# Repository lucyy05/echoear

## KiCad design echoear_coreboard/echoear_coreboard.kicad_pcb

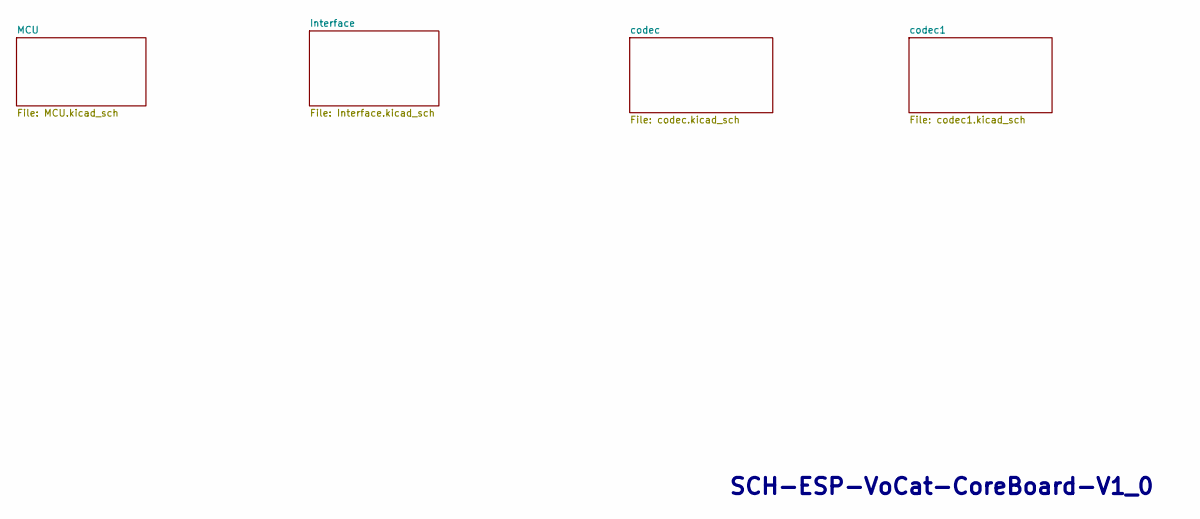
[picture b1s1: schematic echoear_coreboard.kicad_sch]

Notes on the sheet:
SCH-ESP-VoCat-CoreBoard-V1_0

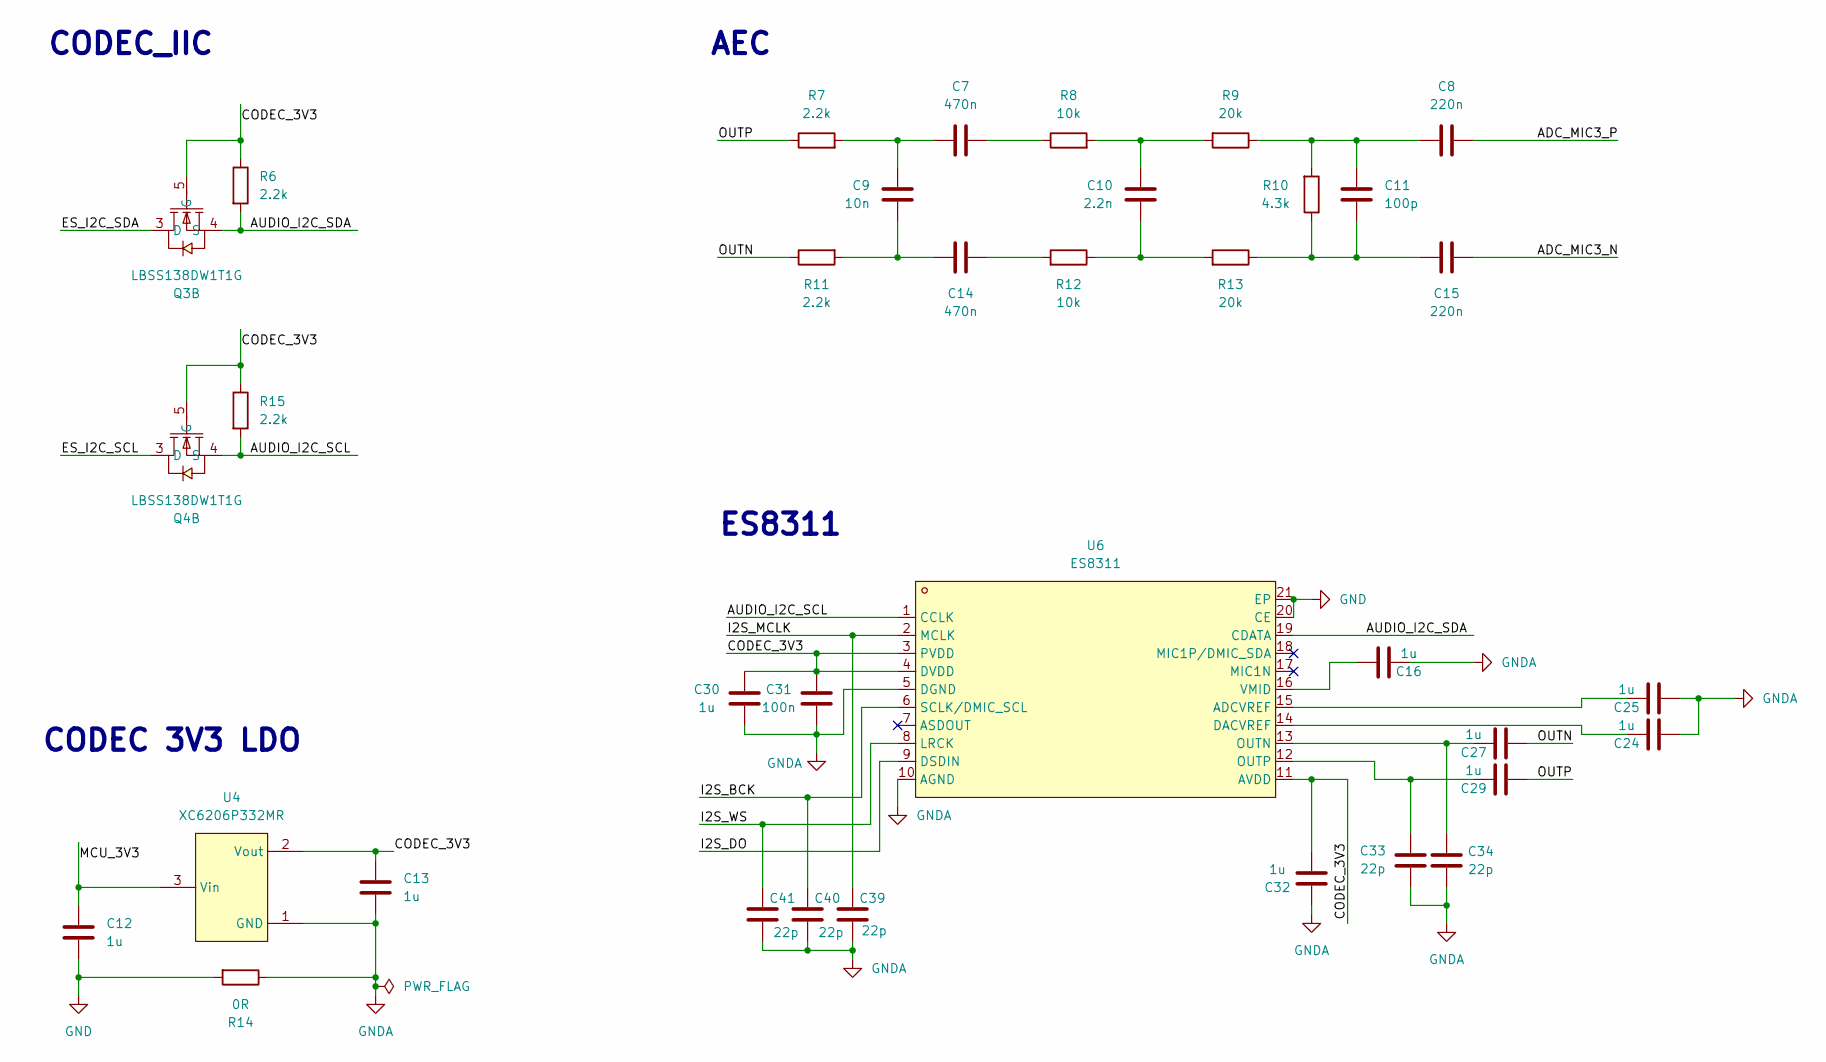
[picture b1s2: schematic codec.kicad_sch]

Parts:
C7, C14: 470n; C_0402_1005Metric; LCSC C437527
C8, C15: 220n; C_0402_1005Metric; LCSC C16772
C9: 10n; C_0402_1005Metric; LCSC C15195
C10: 2.2n; C_0402_1005Metric; LCSC C2987940
C11: 100p; C_0402_1005Metric; LCSC C1546
C12, C13, C16, C24, C25, C27, C29, C30, C32: 1u; C_0402_1005Metric; LCSC C52923
C31: 100n; C_0402_1005Metric; LCSC C1525
C33, C34, C39, C40, C41: 22p; C_0402_1005Metric; LCSC C1555
Q3, Q4: LBSS138DW1T1G; SC-88-6_L2.0-W1.3-P0.65-LS2.1-BL; MPN LBSS138DW1T1G; LCSC Part C525406
R6, R7, R11, R15: 2.2k; R_0402_1005Metric; LCSC C25879
R8, R12: 10k; R_0402_1005Metric; LCSC C25744
R9: 20k; R_0402_1005Metric; LCSC C25765
R10: 4.3k; C_0402_1005Metric; LCSC C477725
R13: 20k; C_0402_1005Metric; LCSC C25765
R14: 0R; R_0402_1005Metric; LCSC C17168
U4: XC6206P332MR; SOT-23-3_L2.9-W1.6-P1.90-LS2.8-BR; MPN XC6206P332MR-G; LCSC Part C5446
U6: ES8311; WQFN-20_L3.0-W3.0-P0.40-BL-EP1.7; MPN ES8311; LCSC Part C962342

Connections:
/codec/ADC_MIC3_N: C15.1
/codec/ADC_MIC3_P: C8.1
/codec/AUDIO_I2C_SCL: Q4.4 (S), R15.2, U6.1 (CCLK)
/codec/AUDIO_I2C_SDA: Q3.4 (S), R6.2, U6.19 (CDATA)
/codec/CODEC_3V3: C13.1, C30.2, C31.2, C32.2, Q3.5 (G), Q4.5 (G), R6.1, R15.1, U4.2 (Vout), U6.3 (PVDD), U6.4 (DVDD), U6.11 (AVDD)
/codec/ES_I2C_SCL: Q4.3 (D)
/codec/ES_I2C_SDA: Q3.3 (D)
/codec/I2S_BCK: C40.2, U6.6 (SCLK/DMIC_SCL)
/codec/I2S_DO: U6.9 (DSDIN)
/codec/I2S_MCLK: C39.2, U6.2 (MCLK)
/codec/I2S_WS: C41.2, U6.8 (LRCK)
/codec/MCU_3V3: C12.1, U4.3 (Vin)
/codec/OUTN: C27.2, R11.1
/codec/OUTP: C29.2, R7.1
GND: C12.2, R14.2, U6.20 (CE), U6.21 (EP); also elsewhere on the board
GNDA: C13.2, C16.2, C24.2, C25.2, C30.1, C31.1, C32.1, C33.1, C34.2, C39.1, C40.1, C41.1, R14.1, U4.1 (GND), U6.5 (DGND), U6.10 (AGND); also elsewhere on the board
unnamed: C7.1, C9.1, R7.2
unnamed: C7.2, R8.1
unnamed: C10.1, R8.2, R9.2
unnamed: C10.2, R12.1, R13.2
unnamed: C8.2, C11.1, R9.1, R10.2
unnamed: C11.2, C15.2, R10.1, R13.1
unnamed: C14.1, R12.2
unnamed: C9.2, C14.2, R11.2
unnamed: C25.1, U6.15 (ADCVREF)
unnamed: C24.1, U6.14 (DACVREF)
unnamed: C27.1, C34.1, U6.13 (OUTN)
unnamed: C29.1, C33.2, U6.12 (OUTP)
unnamed: C16.1, U6.16 (VMID)

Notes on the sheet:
AEC
ES8311
CODEC 3V3 LDO
CODEC_IIC

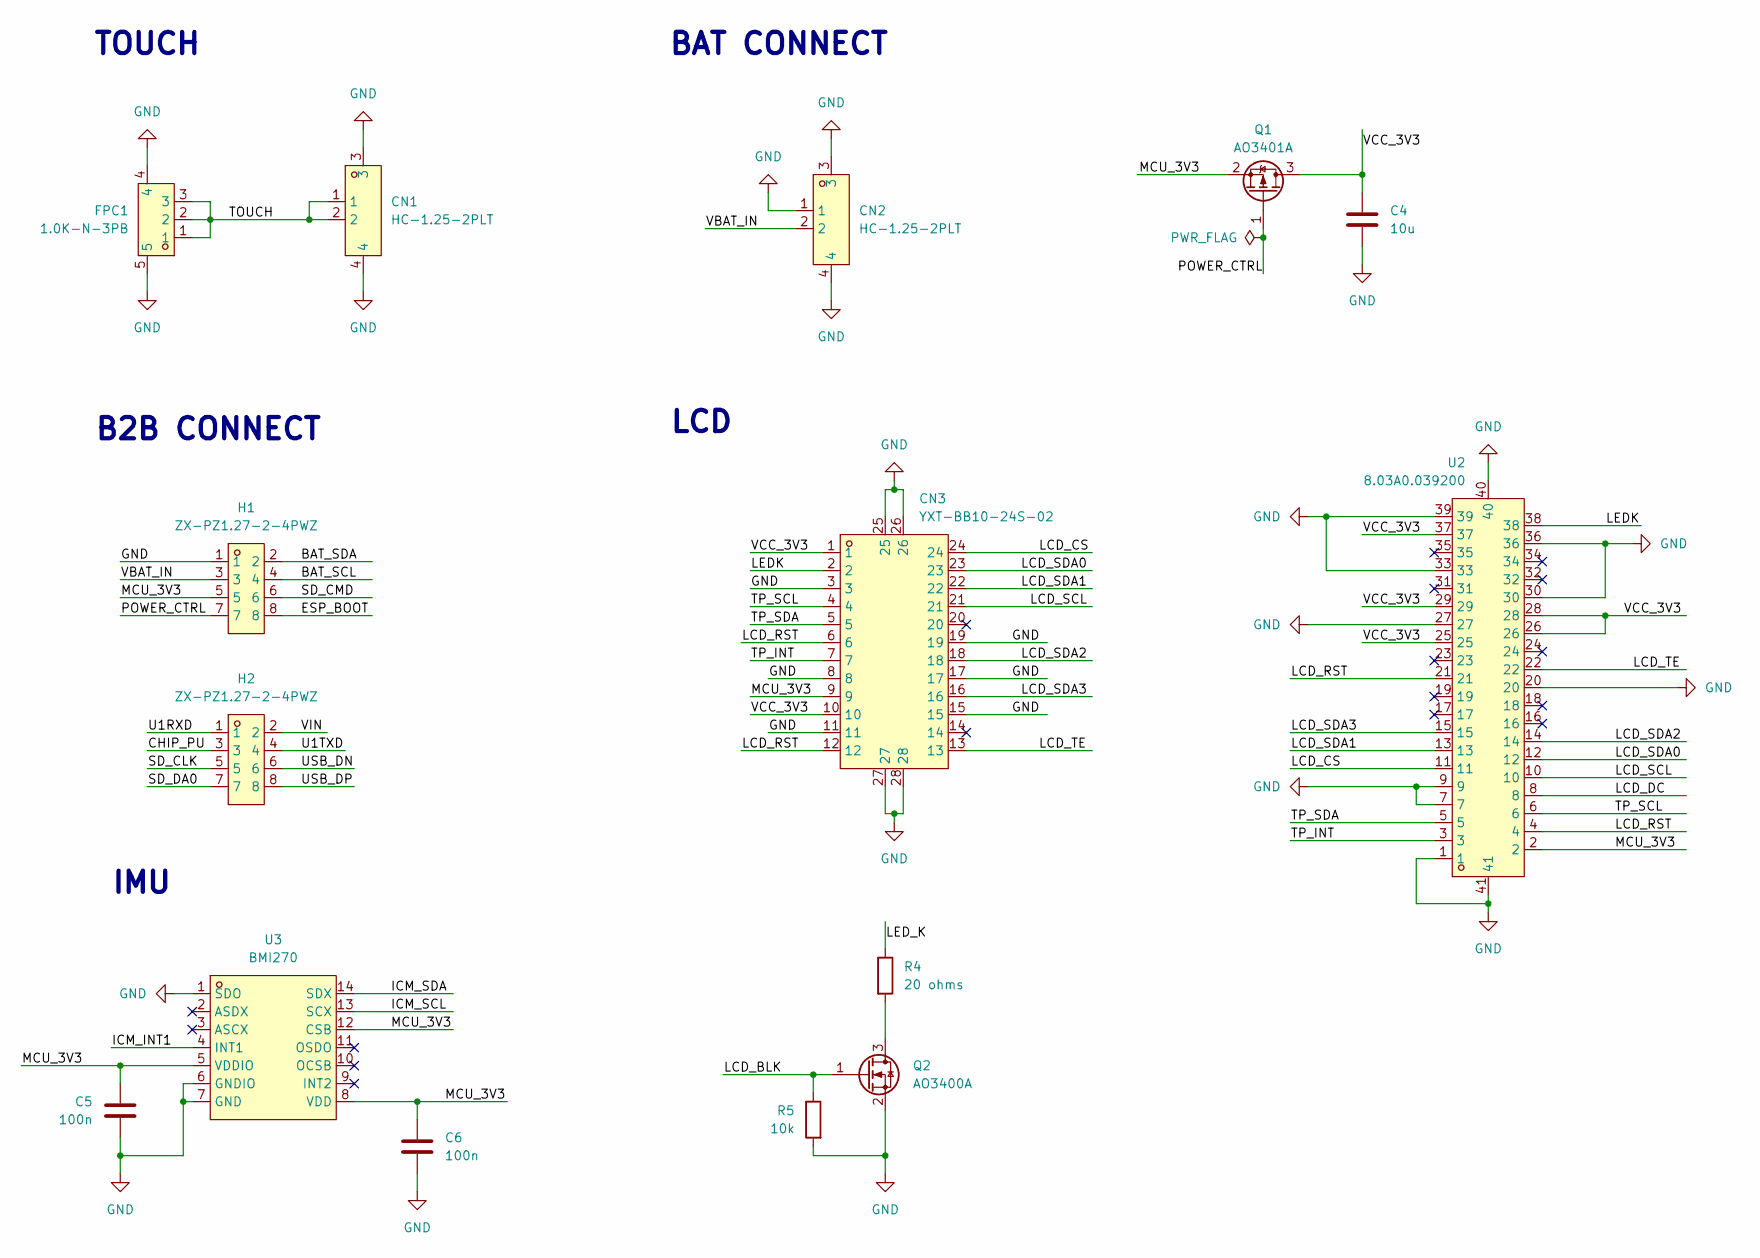
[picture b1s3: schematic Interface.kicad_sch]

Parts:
C4: 10u; C_0603_1608Metric; LCSC C19702
C5, C6: 100n; C_0402_1005Metric; LCSC C1525
CN1, CN2: HC-1.25-2PLT; CONN-SMD_HC-1.25-2PLT; MPN HC-1.25-2PLT; LCSC Part C2845388
CN3: YXT-BB10-24S-02; CONN-SMD_YXT-BB10-24S-02; MPN YXT-BB10-24S-02; LCSC Part C2763965
FPC1: 1.0K-N-3PB; FPC-SMD_3P-P1.00_HDGC_1.0K-N-3PB; MPN 1.0K-N-3PB; LCSC Part C2915549
H1, H2: ZX-PZ1.27-2-4PWZ; HDR-SMD_8P-P1.27-LS5.5_ZX-PZ1.27-2-4PWZ; MPN ZX-PZ1.27-2-4PWZ; LCSC Part C41370772
Q1: AO3401A; SOT-23; LCSC C15127
Q2: AO3400A; SOT-23; LCSC C20917
R4: 20 ohms; R_0402_1005Metric; LCSC C25089
R5: 10k; R_0402_1005Metric; LCSC C25744
U2: 8.03A0.039200; FPC-SMD_39P-P0.60_DIANWEI_8.03A0.039200; MPN 8.03A0.039200; LCSC Part C19188829
U3: BMI270; LGA-14_L3.0-W2.5-P0.50-BR; MPN BMI270; LCSC Part C2836813

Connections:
/Interface/BAT_SCL: H1.4
/Interface/BAT_SDA: H1.2
/Interface/ESP_BOOT: H1.8
/Interface/ICM_INT1: U3.4 (INT1)
/Interface/ICM_SCL: U3.13 (SCX)
/Interface/ICM_SDA: U3.14 (SDX)
/Interface/LCD_BLK: Q2.1 (G), R5.1
/Interface/LCD_CS: CN3.24, U2.11
/Interface/LCD_DC: U2.8
/Interface/LCD_RST: CN3.6, CN3.12, U2.4, U2.21
/Interface/LCD_SCL: CN3.21, U2.10
/Interface/LCD_SDA0: CN3.23, U2.12
/Interface/LCD_SDA1: CN3.22, U2.13
/Interface/LCD_SDA2: CN3.18, U2.14
/Interface/LCD_SDA3: CN3.16, U2.15
/Interface/LCD_TE: CN3.13, U2.22
/Interface/LEDK: CN3.2, U2.38
/Interface/LED_K: R4.1
/Interface/MCU_3V3: C5.2, C6.1, CN3.9, H1.5, Q1.2 (S), U2.2, U3.5 (VDDIO), U3.8 (VDD), U3.12 (CSB)
/Interface/POWER_CTRL: H1.7, Q1.1 (G)
/Interface/SD_CMD: H1.6
/Interface/TOUCH: CN1.1, CN1.2, FPC1.1, FPC1.2, FPC1.3
/Interface/TP_INT: CN3.7, U2.3
/Interface/TP_SCL: CN3.4, U2.6
/Interface/TP_SDA: CN3.5, U2.5
/Interface/VBAT_IN: CN2.2, H1.3
/Interface/VCC_3V3: C4.2, CN3.1, CN3.10, Q1.3 (D), U2.25, U2.26, U2.28, U2.29, U2.37
GND: C4.1, C5.1, C6.2, CN1.3, CN1.4, CN2.1, CN2.3, CN2.4, CN3.3, CN3.8, CN3.11, CN3.15, CN3.17, CN3.19, CN3.25, CN3.26, CN3.27, CN3.28, FPC1.4, FPC1.5, H1.1, Q2.2 (S), R5.2, U2.1, U2.7, U2.9, U2.20, U2.27, U2.30, U2.33, U2.36, U2.39, U2.40, U2.41, U3.1 (SDO), U3.6 (GNDIO), U3.7 (GND); also elsewhere on the board
unnamed: Q2.3 (D), R4.2

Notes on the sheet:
LCD
B2B CONNECT
TOUCH
BAT CONNECT
IMU

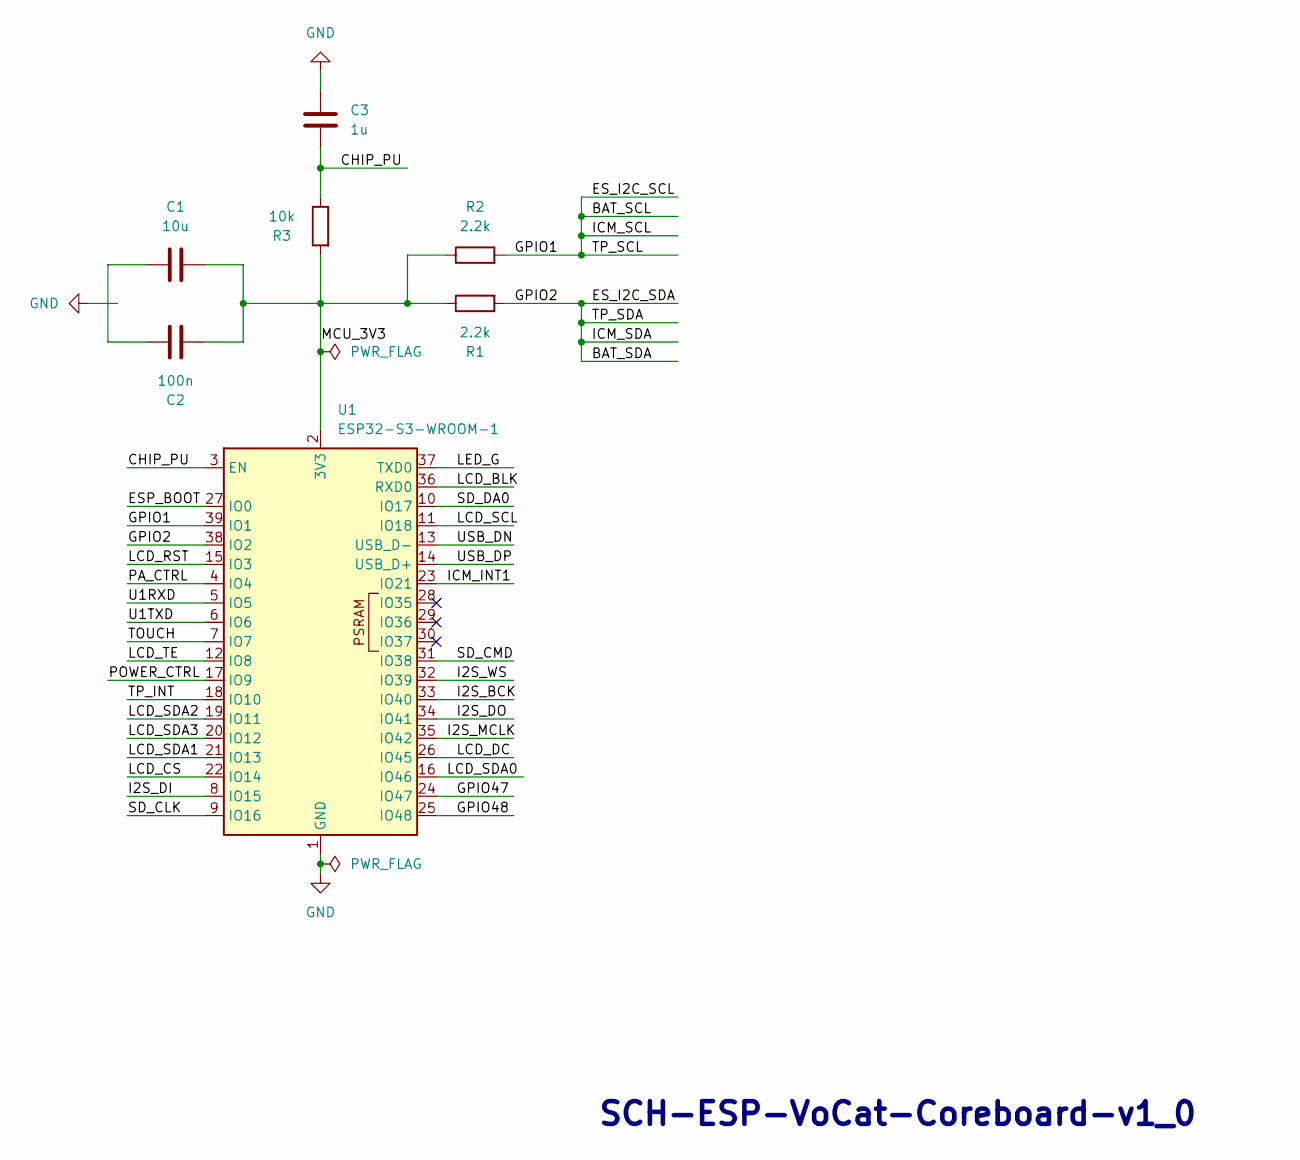
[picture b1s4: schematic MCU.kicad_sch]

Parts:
C1: 10u; C_0603_1608Metric
C2: 100n; C_0402_1005Metric
C3: 1u; C_0402_1005Metric
R1, R2: 2.2k; R_0402_1005Metric
R3: 10k; R_0402_1005Metric
U1: ESP32-S3-WROOM-1; LCSC C2913202

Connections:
/MCU/BAT_SCL: R2.2, U1.39 (IO1)
/MCU/BAT_SDA: R1.2, U1.38 (IO2)
/MCU/CHIP_PU: C3.2, R3.1, U1.3 (EN)
/MCU/ESP_BOOT: U1.27 (IO0)
/MCU/GPIO47: U1.24 (IO47)
/MCU/GPIO48: U1.25 (IO48)
/MCU/I2S_BCK: U1.33 (IO40)
/MCU/I2S_DI: U1.8 (IO15)
/MCU/I2S_DO: U1.34 (IO41)
/MCU/I2S_MCLK: U1.35 (IO42)
/MCU/I2S_WS: U1.32 (IO39)
/MCU/ICM_INT1: U1.23 (IO21)
/MCU/LCD_BLK: U1.36 (RXD0)
/MCU/LCD_CS: U1.22 (IO14)
/MCU/LCD_DC: U1.26 (IO45)
/MCU/LCD_RST: U1.15 (IO3)
/MCU/LCD_SCL: U1.11 (IO18)
/MCU/LCD_SDA0: U1.16 (IO46)
/MCU/LCD_SDA1: U1.21 (IO13)
/MCU/LCD_SDA2: U1.19 (IO11)
/MCU/LCD_SDA3: U1.20 (IO12)
/MCU/LCD_TE: U1.12 (IO8)
/MCU/LED_G: U1.37 (TXD0)
/MCU/MCU_3V3: C1.2, C2.2, R1.1, R2.1, R3.2, U1.2 (3V3)
/MCU/PA_CTRL: U1.4 (IO4)
/MCU/POWER_CTRL: U1.17 (IO9)
/MCU/SD_CLK: U1.9 (IO16)
/MCU/SD_CMD: U1.31 (IO38)
/MCU/SD_DA0: U1.10 (IO17)
/MCU/TOUCH: U1.7 (IO7)
/MCU/TP_INT: U1.18 (IO10)
/MCU/U1RXD: U1.5 (IO5)
/MCU/U1TXD: U1.6 (IO6)
/MCU/USB_DN: U1.13 (USB_D-)
/MCU/USB_DP: U1.14 (USB_D+)
GND: C3.1, U1.1 (GND), U1.40 (GND), U1.41 (GND); also elsewhere on the board
unnamed: C1.1, C2.1

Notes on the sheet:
SCH-ESP-VoCat-Coreboard-v1_0

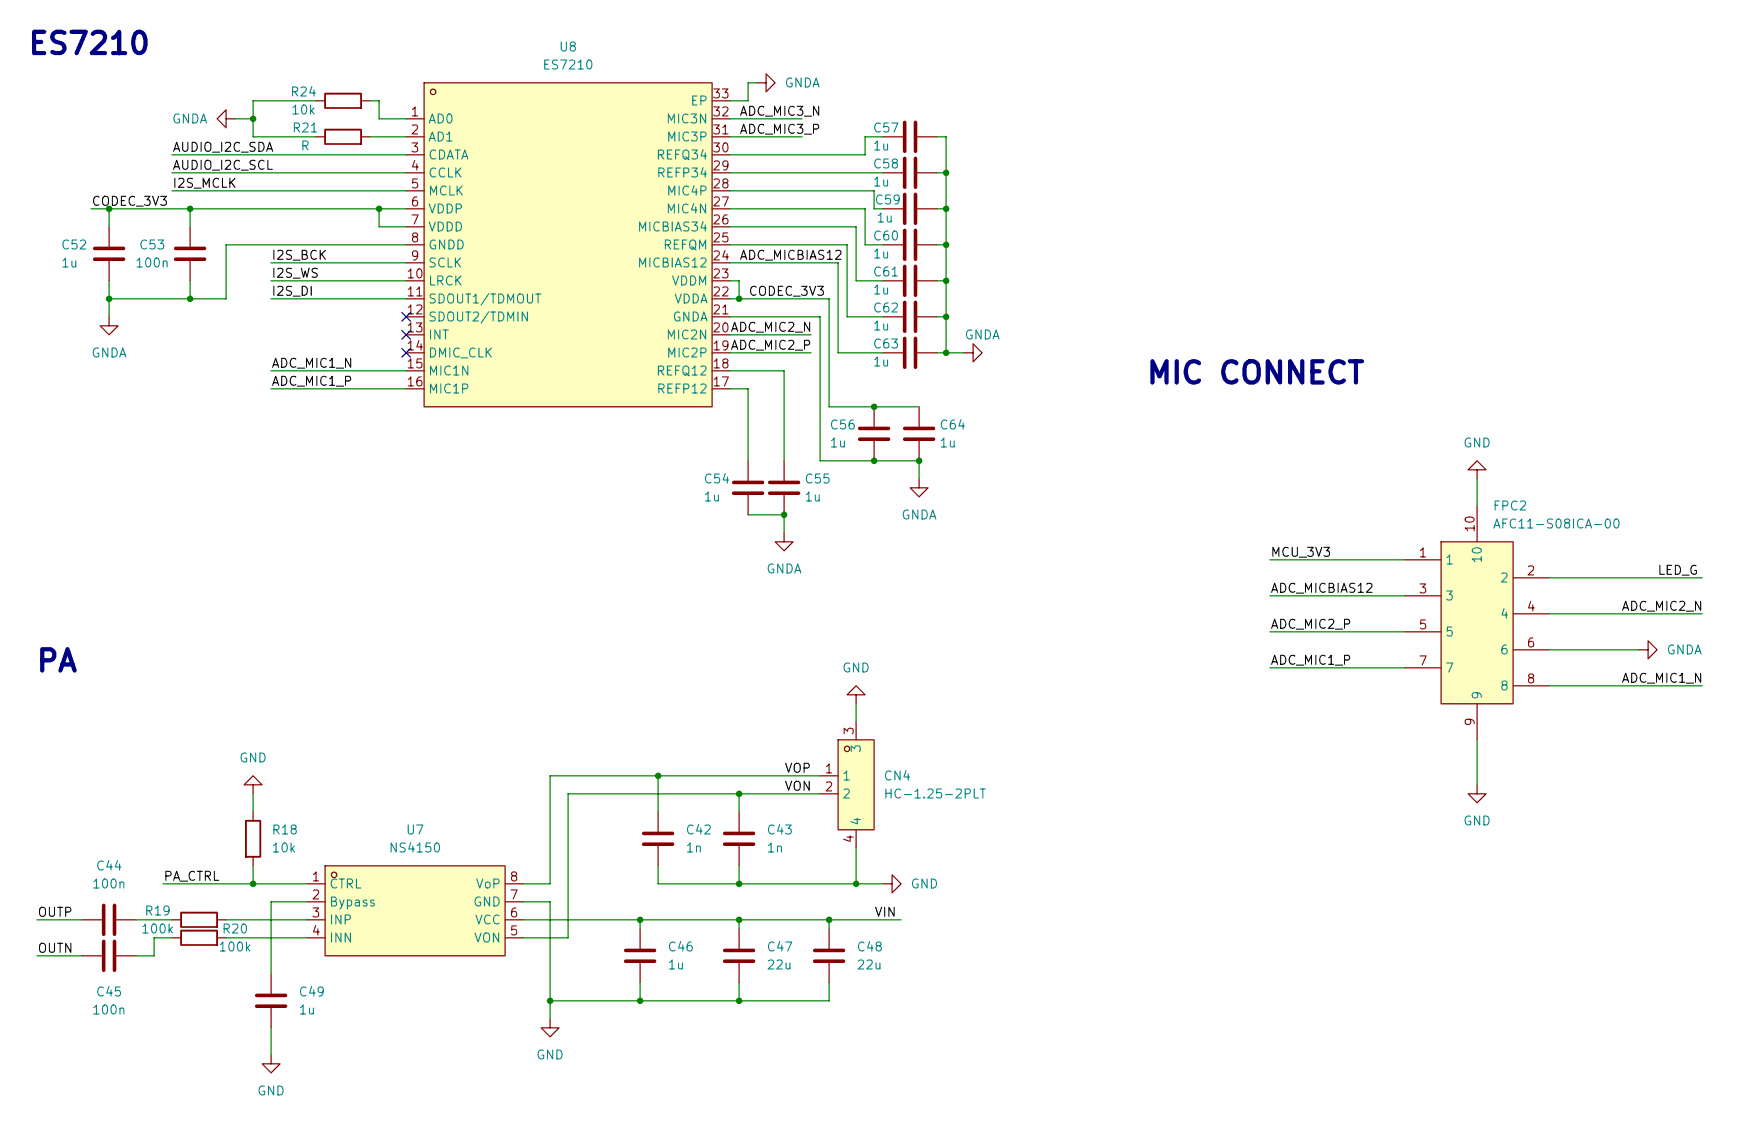
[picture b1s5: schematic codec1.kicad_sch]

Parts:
C42, C43: 1n; C_0402_1005Metric; LCSC C1523
C44, C45, C53: 100n; C_0402_1005Metric; LCSC C1525
C46, C49, C52, C54, C55, C56, C57, C58, C59, C60, C61, C62, C63, C64: 1u; C_0402_1005Metric; LCSC C52923
C47, C48: 22u; C_0603_1608Metric; LCSC C2762594
CN4: HC-1.25-2PLT; CONN-SMD_HC-1.25-2PLT; MPN HC-1.25-2PLT; LCSC Part C2845388
FPC2: AFC11-S08ICA-00; CONN-TH-8P_AFC11-S08ICA-00; MPN AFC11-S08ICA-00; LCSC Part C262497
R18, R24: 10k; R_0402_1005Metric; LCSC C25744
R19, R20: 100k; R_0402_1005Metric; LCSC C25741
R21: R; R_0402_1005Metric; LCSC C25744
U7: NS4150; MSOP-8_L3.0-W3.0-P0.65-LS5.0-BL; MPN NS4150B; LCSC Part C189961
U8: ES7210; QFN-32_L4.0-W4.0-P0.40-BL-EP2.7; MPN ES7210; LCSC Part C365743

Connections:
/codec1/ADC_MIC1_N: FPC2.8, U8.15 (MIC1N); also elsewhere on the board
/codec1/ADC_MIC1_P: FPC2.7, U8.16 (MIC1P); also elsewhere on the board
/codec1/ADC_MIC2_N: FPC2.4, U8.20 (MIC2N); also elsewhere on the board
/codec1/ADC_MIC2_P: FPC2.5, U8.19 (MIC2P); also elsewhere on the board
/codec1/ADC_MIC3_N: U8.32 (MIC3N)
/codec1/ADC_MIC3_P: U8.31 (MIC3P)
/codec1/ADC_MICBIAS12: C63.1, FPC2.3, U8.24 (MICBIAS12); also elsewhere on the board
/codec1/AUDIO_I2C_SCL: U8.4 (CCLK)
/codec1/AUDIO_I2C_SDA: U8.3 (CDATA)
/codec1/CODEC_3V3: C52.1, C53.2, C56.1, C64.1, U8.6 (VDDP), U8.7 (VDDD), U8.22 (VDDA), U8.23 (VDDM)
/codec1/I2S_BCK: U8.9 (SCLK)
/codec1/I2S_DI: U8.11 (SDOUT1/TDMOUT)
/codec1/I2S_MCLK: U8.5 (MCLK)
/codec1/I2S_WS: U8.10 (LRCK)
/codec1/OUTN: C45.1
/codec1/OUTP: C44.2
/codec1/PA_CTRL: R18.2, U7.1 (CTRL)
/codec1/VIN: C46.1, C47.1, C48.1, U7.6 (VCC)
/codec1/VON: C43.1, CN4.2, U7.5 (VON)
/codec1/VOP: C42.1, CN4.1, U7.8 (VoP)
GND: C42.2, C43.2, C46.2, C47.2, C48.2, C49.2, CN4.3, CN4.4, FPC2.9, FPC2.10, R18.1, U7.7 (GND); also elsewhere on the board
GNDA: C52.2, C53.1, C54.2, C55.2, C56.2, C57.2, C58.2, C59.2, C60.2, C61.2, C62.2, C63.2, C64.2, FPC2.6, R21.1, R24.1, U8.8 (GNDD), U8.21 (GNDA), U8.33 (EP); also elsewhere on the board
unnamed: C44.1, R19.1
unnamed: C45.2, R20.1
unnamed: C49.1, U7.2 (Bypass)
unnamed: R20.2, U7.4 (INN)
unnamed: R19.2, U7.3 (INP)
unnamed: R24.2, U8.1 (AD0)
unnamed: R21.2, U8.2 (AD1)
unnamed: C60.1, U8.27 (MIC4N)
unnamed: C59.1, U8.28 (MIC4P)
unnamed: C61.1, U8.26 (MICBIAS34)
unnamed: C54.1, U8.17 (REFP12)
unnamed: C58.1, U8.29 (REFP34)
unnamed: C55.1, U8.18 (REFQ12)
unnamed: C57.1, U8.30 (REFQ34)
unnamed: C62.1, U8.25 (REFQM)

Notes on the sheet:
MIC CONNECT
ES7210

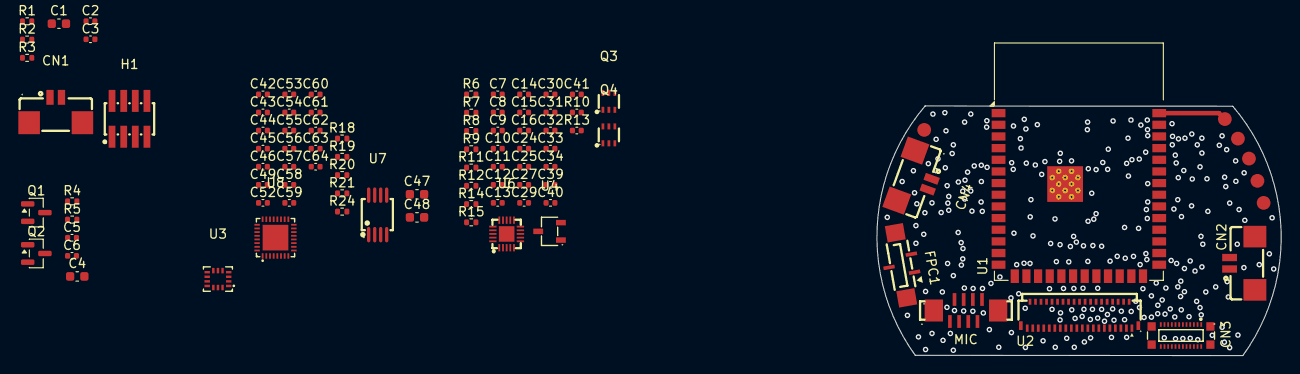
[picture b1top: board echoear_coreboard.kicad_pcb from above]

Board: 4 copper layers, 44.0 x 27.2 mm, 87 parts (0 on the bottom side), 73 nets.

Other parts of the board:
MIC: AFC11-S08ICA-00; CONN-TH-8P_AFC11-S08ICA-00

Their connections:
/codec1/ADC_MIC1_N: MIC.8; also elsewhere on the board
/codec1/ADC_MIC1_P: MIC.7; also elsewhere on the board
/codec1/ADC_MIC2_N: MIC.4; also elsewhere on the board
/codec1/ADC_MIC2_P: MIC.5; also elsewhere on the board
/codec1/ADC_MICBIAS12: MIC.3; also elsewhere on the board
GND: MIC.9, MIC.10; also elsewhere on the board
GNDA: MIC.6; also elsewhere on the board

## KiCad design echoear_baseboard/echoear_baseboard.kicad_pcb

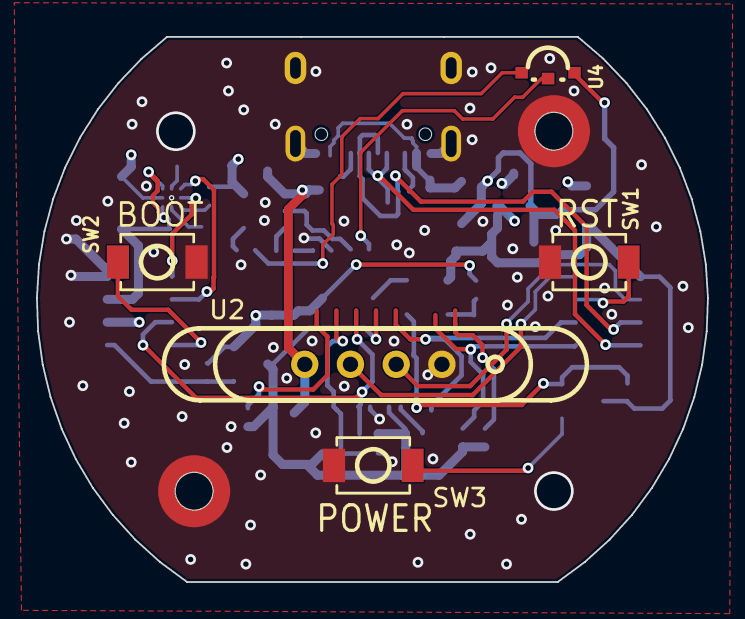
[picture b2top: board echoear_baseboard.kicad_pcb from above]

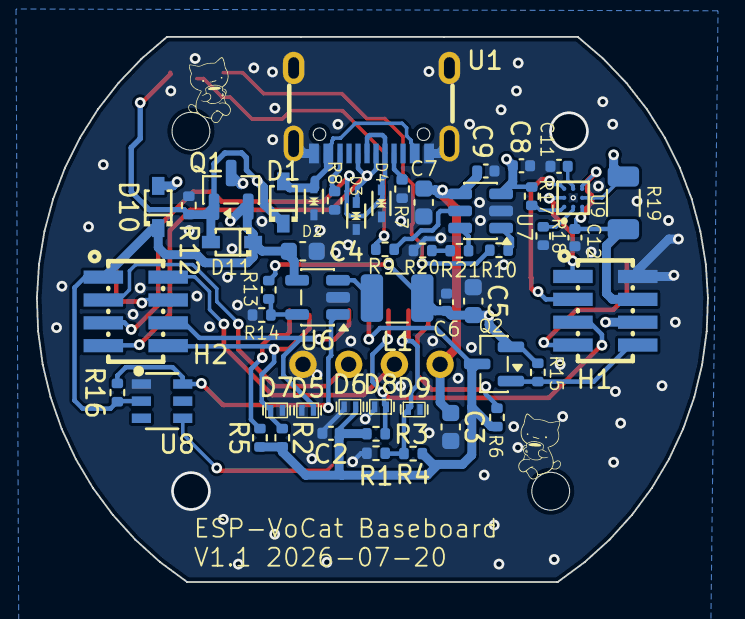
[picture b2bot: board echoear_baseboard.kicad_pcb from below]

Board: 4 copper layers, 37.3 x 30.3 mm, 58 parts (51 on the bottom side), 36 nets.

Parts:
C2, C6: 100n; C_0402_1005Metric
C3, C4, C5, C7: 10u; C_0603_1608Metric
C8, C9: 10u; C_0402_1005Metric
C11: 2.2u; C_0402_1005Metric
C12: 1u; C_0402_1005Metric
D1, D10, D11: 1N5819WS; SOD-323_L1.8-W1.3-LS2.5-RD
D2, D3, D4: ESD131-B1-W0201; SOD-523_L1.2-W0.8-LS1.6-BI
D5, D6, D7, D8, D9: ESD131-B1-W0201; SOD-882_L1.0-W0.6-BI
H1, H2: Conn_02x04_Odd_Even; HDR-SMD_8P-P1.27-V-F-R2-C4-LS4.8
L1: 2.2u; L_1210_3225Metric
Q1, Q2: AO3401A; SOT-23
R1: 51k; R_0402_1005Metric
R2, R3, R4, R5, R6, R15, R18: 10k; R_0402_1005Metric
R7, R8: 5.1k; R_0402_1005Metric
R9, R10, R16: 4.7k; R_0402_1005Metric
R12: 10M; R_0402_1005Metric
R13, R17: 100k; R_0402_1005Metric
R14: 22.1k; R_0402_1005Metric
R19: 10m; R_1206_3216Metric
R20: 1.5k; R_0402_1005Metric
R21: 1k; R_0402_1005Metric
SW1, SW2, SW3: TS-1088-AR02016; SW-SMD_L3.9-W3.0-P4.45
U1: TYPE-C 16PIN 2MD(073); USB-C-SMD_TYPE-C-16PIN-2MD-073
U2: YZ92015035T-04025-01; MFP_磁吸母座_4P
U3, U5: MountingHole_Pad; Mounting_Wuerth_WA-SMSI-M1.6_H1mm_9774010633
U4: A-SP1102DR6GHC-C01-2C; LED-SMD_3P-L3.0-W1.5_A-SP1102DR6W1D-C01-2C
U6: TLV62569DBV; SOT-23-5
U7: TP4057; TSOT-23-6
U8: SAM8108; SOT-23-6_L2.9-W1.6-P0.95-LS2.8-BL
U9: DSBGA-9_L1.7-W1.6-R3-C3-P0.50-BL

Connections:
/BAT_SCL: H1.3, U9.A3 (SCL)
/BAT_SDA: H1.1, U9.A2 (SDA)
/CHRG: R10.1, U7.1 (~CHRG)
/ESP_BOOT: H1.7, SW2.1 (A)
/ESP_RST: H2.4, SW1.1 (A)
/MCU_3V3: C5.1, C6.1, H1.6, L1.2, Q2.2 (S), R13.1, R15.1
/POWER_CTRL: H1.8, Q2.1 (G), R15.2
/PWR_EN: R16.2, U6.1 (EN), U8.6 (OUT)
/SD_CLK: D5.1 (A1), H2.6
/SD_CMD: D8.1 (A1), H1.5, R3.2
/SD_DA0: D7.1 (A1), H2.8, R2.2
/STDBY: R9.1, U7.5 (STDBY)
/U1RXD: H2.2, U2.2
/U1TXD: H2.3, U2.3
/USB_DN: D4.1 (A1), H2.5, U1.A7 (Dn1), U1.B7 (Dn2)
/USB_DP: D3.1 (A1), H2.7, U1.A6 (Dp1), U1.B6 (Dp2)
/VBAT: C8.1, D10.2 (A), Q1.3 (D), R17.2, R19.2, U7.3 (BAT), U9.C2 (SRN)
/VBAT_IN: C12.1, H1.4, R19.1, U9.C1 (SRP), U9.C3 (BAT)
/VBUS: C3.2, C7.1, C9.1, D1.1 (K), D11.2 (A), Q1.1 (G), R12.1, U2.1, U4.1 (A), U7.4 (V_{CC})
/VBUS_IN: D1.2 (A), D2.1 (A1), U1.A4B9 (VBUS), U1.B4A9 (VBUS)
/VCC_3V3: C2.1, D6.1 (A1), Q2.3 (D), R2.1, R3.1, R4.1, R5.1, R6.1
/VIN: C4.1, D10.1 (K), D11.1 (K), H2.1, Q1.2 (S), R16.1, U6.4 (VIN), U8.2 (VDD)
GND: C2.2, C3.1, C4.2, C5.2, C6.2, C7.2, C8.2, C9.2, C11.2, C12.2, D2.2 (A2), D3.2 (A2), D4.2 (A2), D5.2 (A2), D6.2 (A2), D7.2 (A2), D8.2 (A2), D9.2 (A2), H1.2, R1.1, R7.2, R8.2, R12.2, R14.2, R18.1, R20.1, SW1.2 (B), SW2.2 (B), SW3.2 (B), U1.13 (EH), U1.14 (EH), U1.A1B12 (GND), U1.B1A12 (GND), U2.4, U3.1 (1_1), U5.1 (1_1), U6.2 (GND), U7.2 (GND), U8.1 (GND), U9.B2 (VSS)
unnamed: D9.1 (A1), R1.2, R4.2
unnamed: R9.2, U4.2 (K)
unnamed: R10.2, U4.3 (K)
unnamed: R20.2, R21.2
unnamed: SW3.1 (A), U8.4 (ONOFF)
unnamed: R7.1, U1.A5 (CC1)
unnamed: R8.1, U1.B5 (CC2)
unnamed: R13.2, R14.1, U6.5 (FB)
unnamed: L1.1, U6.3 (SW)
unnamed: R21.1, U7.6 (PROG)
unnamed: R18.2, U9.B1 (BIN)
unnamed: R17.1, U9.A1 (GPOUT)
unnamed: C11.1, U9.B3 (VDD)

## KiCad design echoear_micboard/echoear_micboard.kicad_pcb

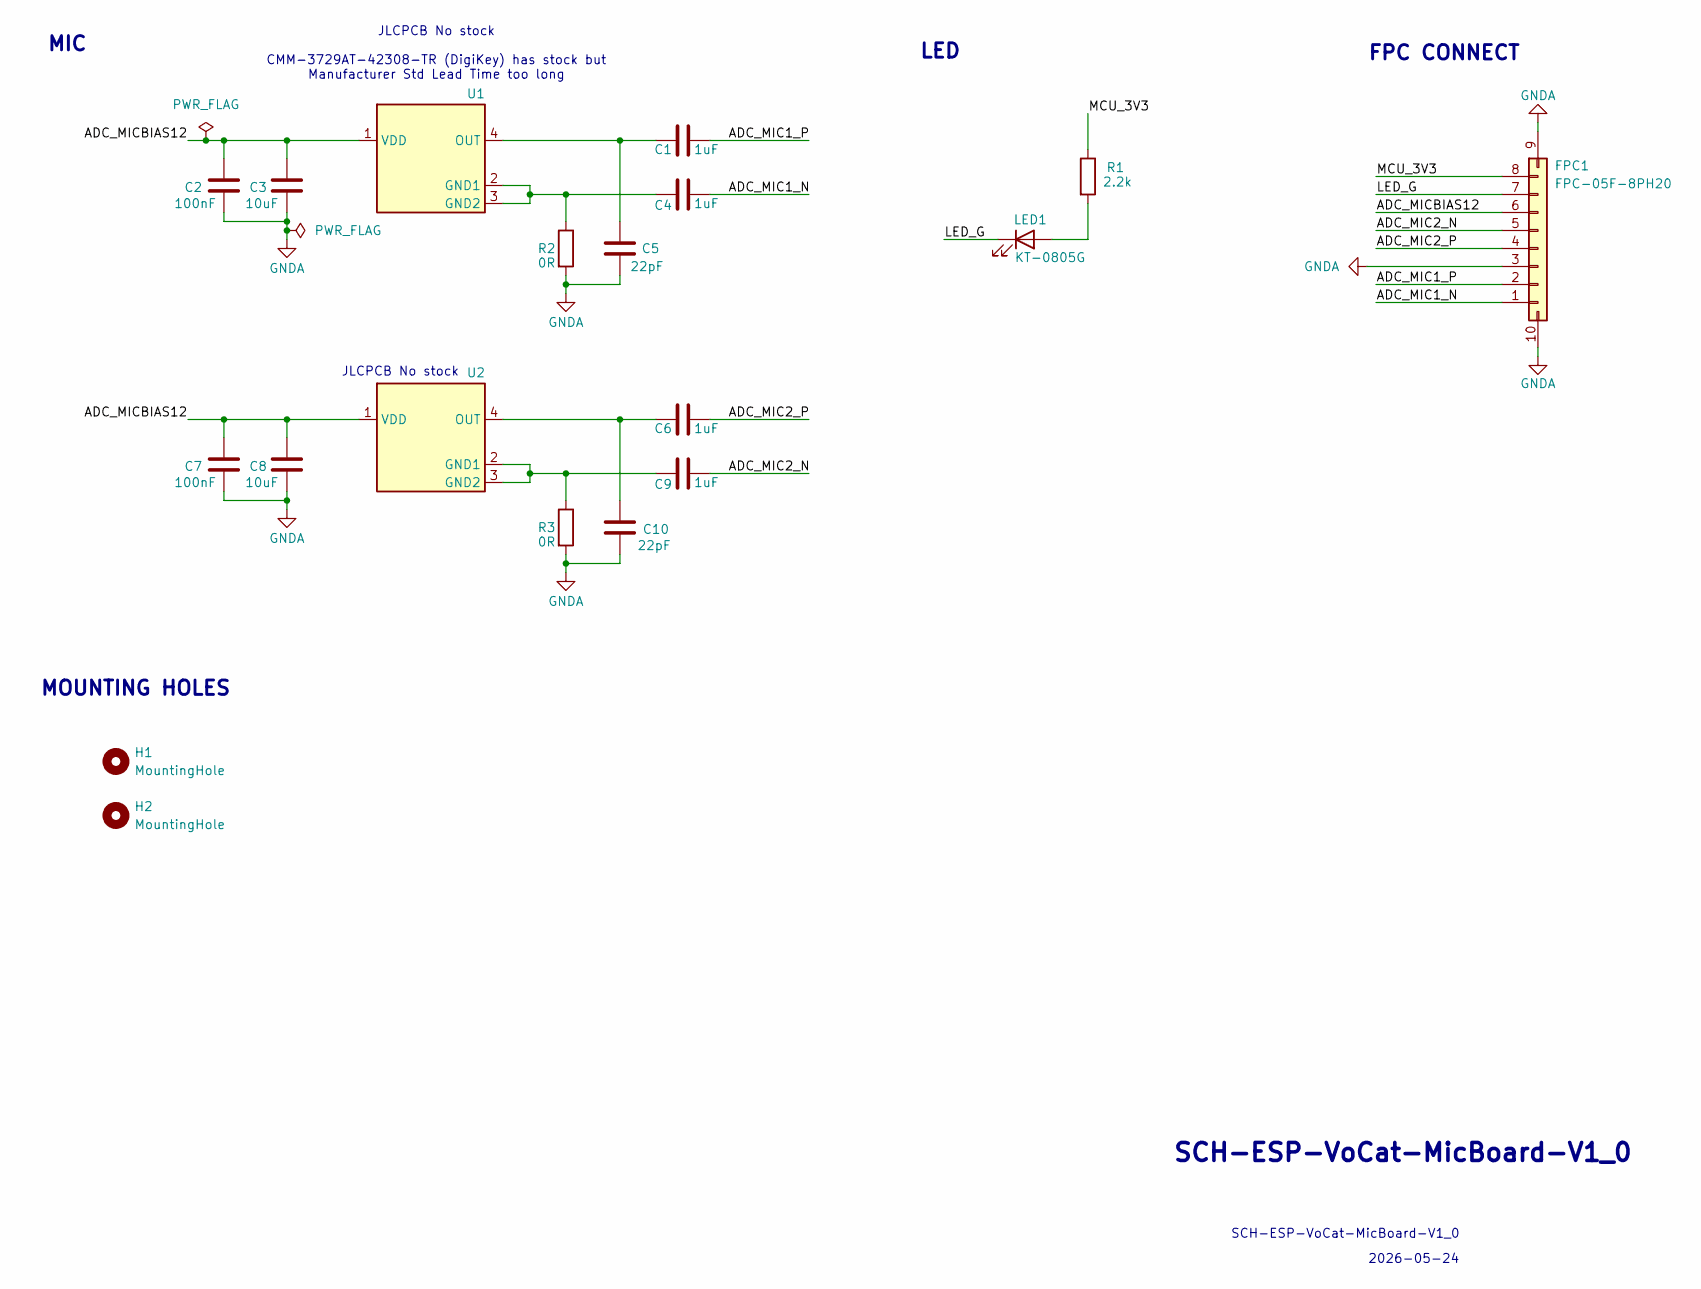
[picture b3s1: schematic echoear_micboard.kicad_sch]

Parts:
C1, C4, C6, C9: 1uF; C_0402_1005Metric; LCSC C52923
C2, C7: 100nF; C_0402_1005Metric; LCSC C1525
C3, C8: 10uF; C_0402_1005Metric; LCSC C7472949
C5, C10: 22pF; C_0402_1005Metric; LCSC C1555
FPC1: FPC-05F-8PH20; LCSC C2856797
H1, H2: MountingHole; MountingHole_2.2mm_M2
LED1: KT-0805G; LED0805-R-RD; LCSC C2297
R1: 2.2k; R_0402_1005Metric; LCSC C25879
R2, R3: 0R; R_0402_1005Metric; LCSC C17168
U1, U2: MIC_CMM-3729AT-42308-TR; LCSC C3171805

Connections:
/ADC_MIC1_N: C4.2, FPC1.1
/ADC_MIC1_P: C1.2, FPC1.2
/ADC_MIC2_N: C9.2, FPC1.5
/ADC_MIC2_P: C6.2, FPC1.4
/ADC_MICBIAS12: C2.2, C3.2, C7.2, C8.2, FPC1.6, U1.1 (VDD), U2.1 (VDD)
/LED_G: FPC1.7, LED1.1 (K)
/MCU_3V3: FPC1.8, R1.1
GNDA: C2.1, C3.1, C5.1, C7.1, C8.1, C10.1, FPC1.3, FPC1.9 (AGND), FPC1.10, R2.2, R3.2
unnamed: LED1.2 (A), R1.2
unnamed: C4.1, R2.1, U1.2 (GND1), U1.3 (GND2)
unnamed: C1.1, C5.2, U1.4 (OUT)
unnamed: C9.1, R3.1, U2.2 (GND1), U2.3 (GND2)
unnamed: C6.1, C10.2, U2.4 (OUT)

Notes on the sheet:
SCH-ESP-VoCat-MicBoard-V1_0
MOUNTING HOLES
2026-05-24
MIC
JLCPCB No stock
JLCPCB No stock CMM-3729AT-42308-TR (DigiKey) has stock but Manufacturer Std Lead Time too long
LED
FPC CONNECT

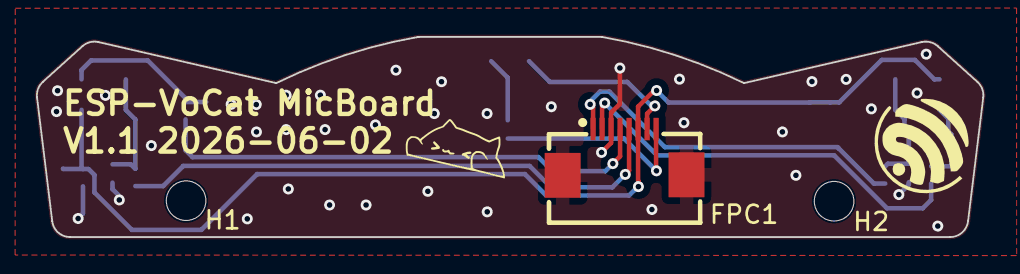
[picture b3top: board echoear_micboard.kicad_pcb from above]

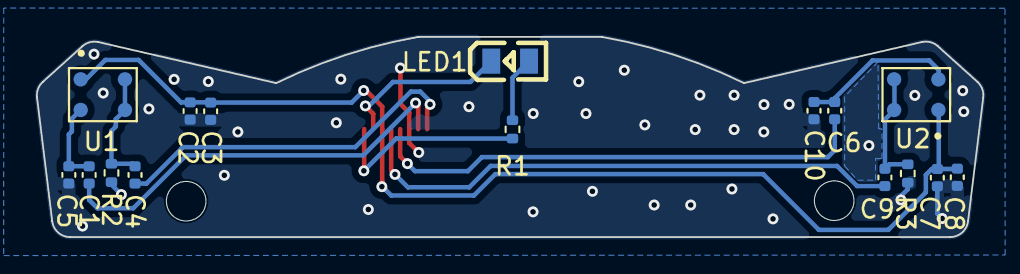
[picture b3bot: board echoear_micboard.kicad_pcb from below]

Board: 2 copper layers, 52.6 x 11.1 mm, 19 parts (16 on the bottom side), 13 nets.
